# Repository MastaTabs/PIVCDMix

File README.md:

# PIV CDMix

This little gem was developed at Village Tronic Computer back in the day by a service technician,
after the audio circuits of the PicassoIV was chiseled in stone and had some short comings.

Using this board you can listen to CD and Amiga audio through the PIV audio output at the same time.

The design is proven and working.

 <-- You may order some PCB's here.

### License
The "PIV CDMix" documentation, including the design itself, is copyright © MastaTabs (Tobias Seiler) 2020.

"PIV CDMix" is Open Hardware licensed under the CERN OHL v. 1.2.

You may redistribute and modify this documentation under the terms of the CERN OHL v.1.2. This documentation is distributed as is and WITHOUT ANY EXPRESS OR IMPLIED WARRANTIES whatsoever with respect to its functionality, operability or use, including, without limitation, any implied warranties OF MERCHANTABILITY, SATISFACTORY QUALITY, FITNESS FOR A PARTICULAR PURPOSE or infringement. We expressly disclaim any liability whatsoever for any direct, indirect, consequential, incidental or special damages, including, without limitation, lost revenues, lost profits, losses resulting from business interruption or loss of data, regardless of the form of action or legal theory under which the liability may be asserted, even if advised of the possibility or likelihood of such damages.

A copy of the full license is included in file LICENSE.pdf, please refer to it for applicable conditions. In order to properly deal with its terms, please see file LICENSE_HOWTO.pdf.

The contact points for information about manufactured Products (see section 4.2) are listed in file PRODUCT.md.

Any modifications made by Licensees (see section 3.4.b) shall be recorded in file CHANGES.md.

The Documentation Location of the original project is https://github.com/MastaTabs/PIVCDMix.

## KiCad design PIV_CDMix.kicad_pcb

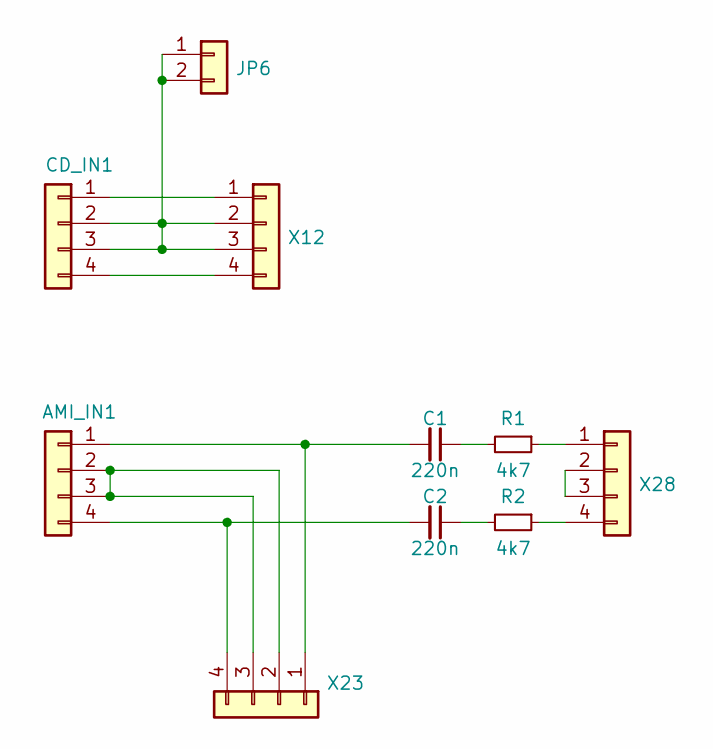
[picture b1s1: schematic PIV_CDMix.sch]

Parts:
AMI_IN1: Conn_01x04; Pin_Header_Angled_1x04_Pitch2.54mm
C1, C2: 220n; C_0805_HandSoldering
CD_IN1: Conn_01x04; Pin_Header_Angled_1x04_Pitch2.54mm
JP6: Conn_01x02; Socket_Strip_Straight_1x02_Pitch2.54mm
R1, R2: 4k7; R_0805_HandSoldering
X12, X23, X28: Conn_01x04; Socket_Strip_Straight_1x04_Pitch2.54mm

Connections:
unnamed: AMI_IN1.1, C1.2, X23.1
unnamed: AMI_IN1.2, AMI_IN1.3, X23.2, X23.3
unnamed: AMI_IN1.4, C2.2, X23.4
unnamed: C1.1, R1.2
unnamed: C2.1, R2.2
unnamed: CD_IN1.1, X12.1
unnamed: CD_IN1.2, CD_IN1.3, JP6.1, JP6.2, X12.2, X12.3
unnamed: CD_IN1.4, X12.4
unnamed: R1.1, X28.1
unnamed: R2.1, X28.4
unnamed: X28.2, X28.3

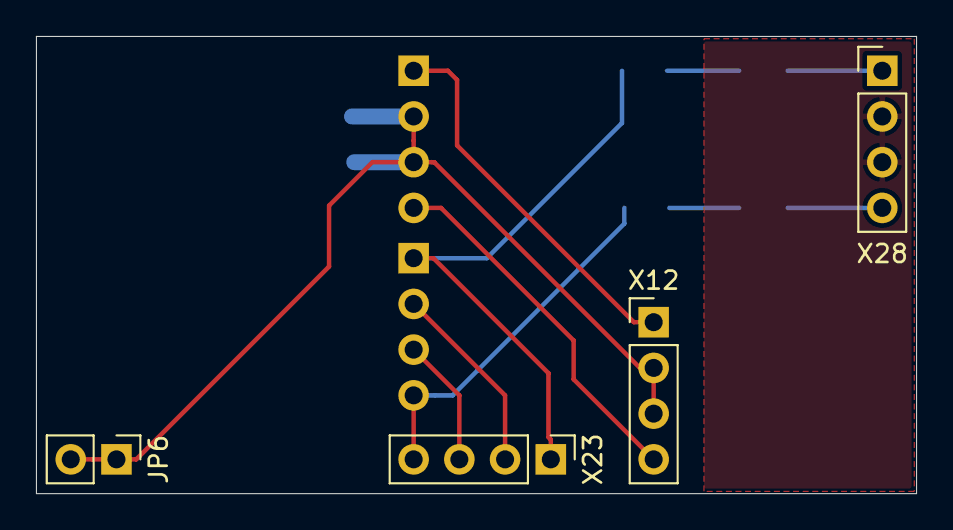
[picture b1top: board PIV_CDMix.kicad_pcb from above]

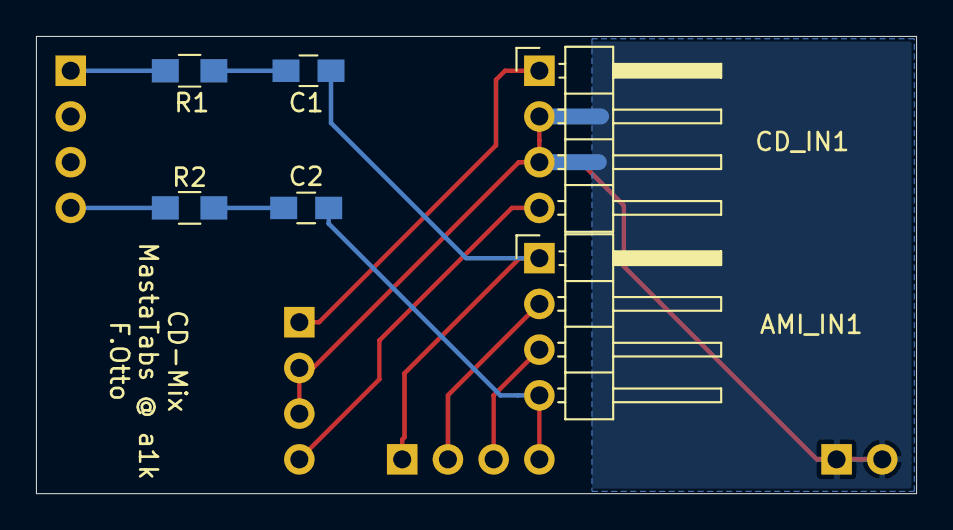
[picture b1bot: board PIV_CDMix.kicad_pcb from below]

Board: 2 copper layers, 48.9 x 25.4 mm, 10 parts (6 on the bottom side), 11 nets.

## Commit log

2020-05-30 add License HowTo
2020-05-30 added BOM
2022-10-12 Update README.md
    Add link to PCBWay project site.
